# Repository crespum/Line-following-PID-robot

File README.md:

Line following robot
========================

This robot was developed for the [OSHWDem 2014](http://oshwdem.org/ "OSHWDem A Coruña") by Mateo Ramos and Xabi Crespo. It has two functionalities:
+ Obviously, it completes a circuit following a black line based on a PID algorithm.
+ It connects to an Android app through bluetooth and sends data about the wheels speed so that the Android phone can draw the circuit.

Repository structure
------------------------
This project is divided into three main folders:
+ [Electronics](https://github.com/xcrespo/Line-following-PID-robot/tree/master/Electronics): contains the design of all the PCBs including wheels encoders, infrared sensors and one last board which contains the motor drivers, headers for the Bluetooth board and headers for a Arduino mini pro.
+ [Android/BluetoothManager](https://github.com/xcrespo/Line-following-PID-robot/tree/master/Android/BluetoothManager): contains the Android app in charge of communicating with the robot and print the circuit.
+ [Arduino/robot](https://github.com/xcrespo/Line-following-PID-robot/tree/master/Arduino/robot): contains the Arduino sketch

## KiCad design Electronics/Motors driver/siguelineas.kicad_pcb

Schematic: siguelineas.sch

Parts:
IC1: L293D; stepper drivers-DIL16
P1: CONN_10X2
P2: CONN_4
U1: ARDUINO-DEEK-ROBOT

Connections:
/BAT: IC1.1 (1,2EN), IC1.9 (3,4EN), IC1.16 (VCC1), P1.20, P2.1, U1.30
/BAT_MOTORS: IC1.8 (VCC2), P1.1
/C1L: IC1.2 (1A), U1.5
/C1R: IC1.7 (2A), U1.6
/C2L: IC1.10 (3A), U1.10
/C2R: IC1.15 (4A), U1.11
/M1L: IC1.3 (1Y), P1.5
/M1R: IC1.6 (2Y), P1.3
/M2L: IC1.14 (4Y), P1.6
/M2R: IC1.11 (3Y), P1.4
/PIN2: P1.17, U1.2
/PIN3: P1.15, U1.3
/PIN4: P1.13, U1.4
/PIN7: P1.11, U1.7
/PIN8: P1.9, U1.8
/PIN9: P1.7, U1.9
GND: IC1.4 (GND1), IC1.5 (GND2), IC1.12 (GND4), IC1.13 (GND3), P1.2, P1.19, P2.2, U1.32, U1.33, U1.34, U1.35, U1.36
unnamed: P2.3, U1.19
unnamed: P2.4, U1.18

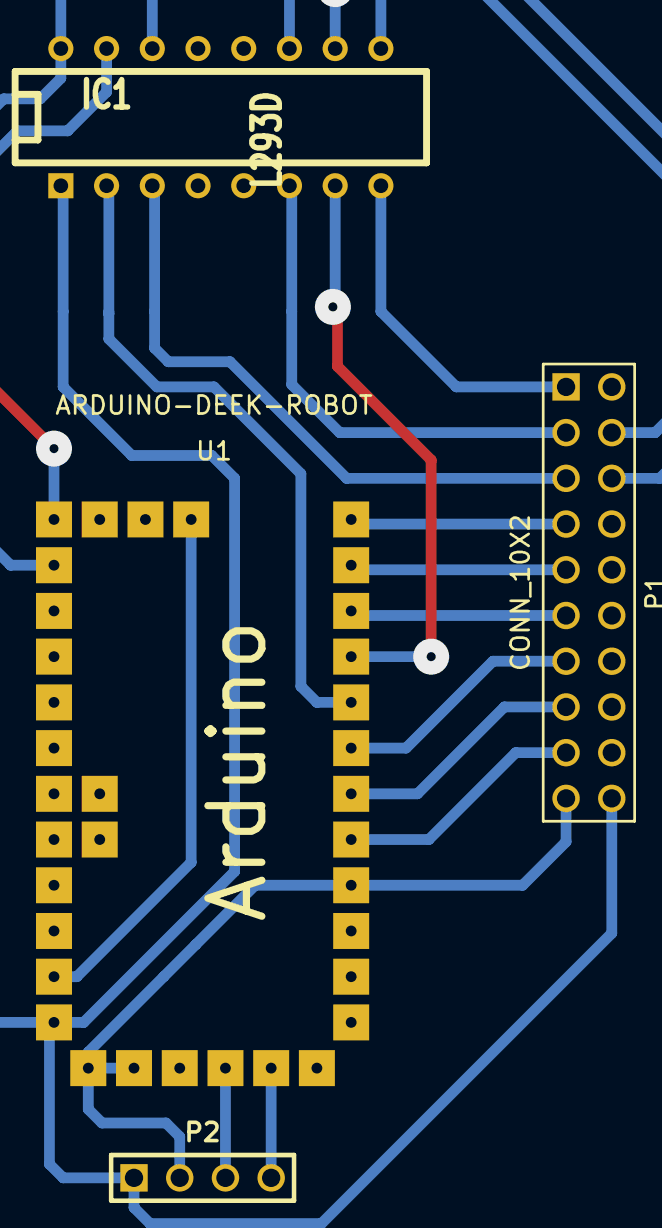
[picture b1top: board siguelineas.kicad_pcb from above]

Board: 2 copper layers, 4 parts (0 on the bottom side), 19 nets.

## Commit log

2014-11-18 Android binary files removed
2014-11-18 .gitignore added
2014-11-29 added new media
2014-11-29 Readme created Folders renamed
